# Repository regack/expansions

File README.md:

expansions
==========

Keyboard Expansion Boards

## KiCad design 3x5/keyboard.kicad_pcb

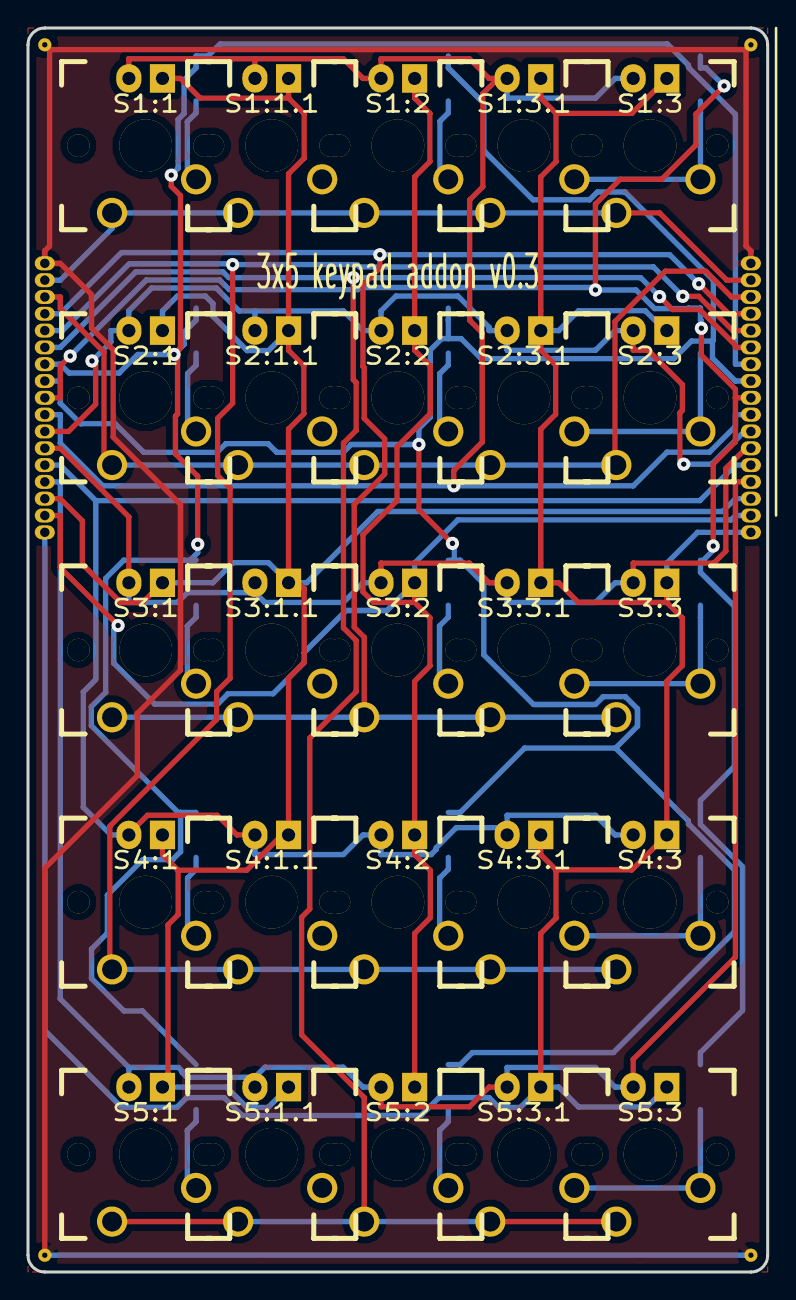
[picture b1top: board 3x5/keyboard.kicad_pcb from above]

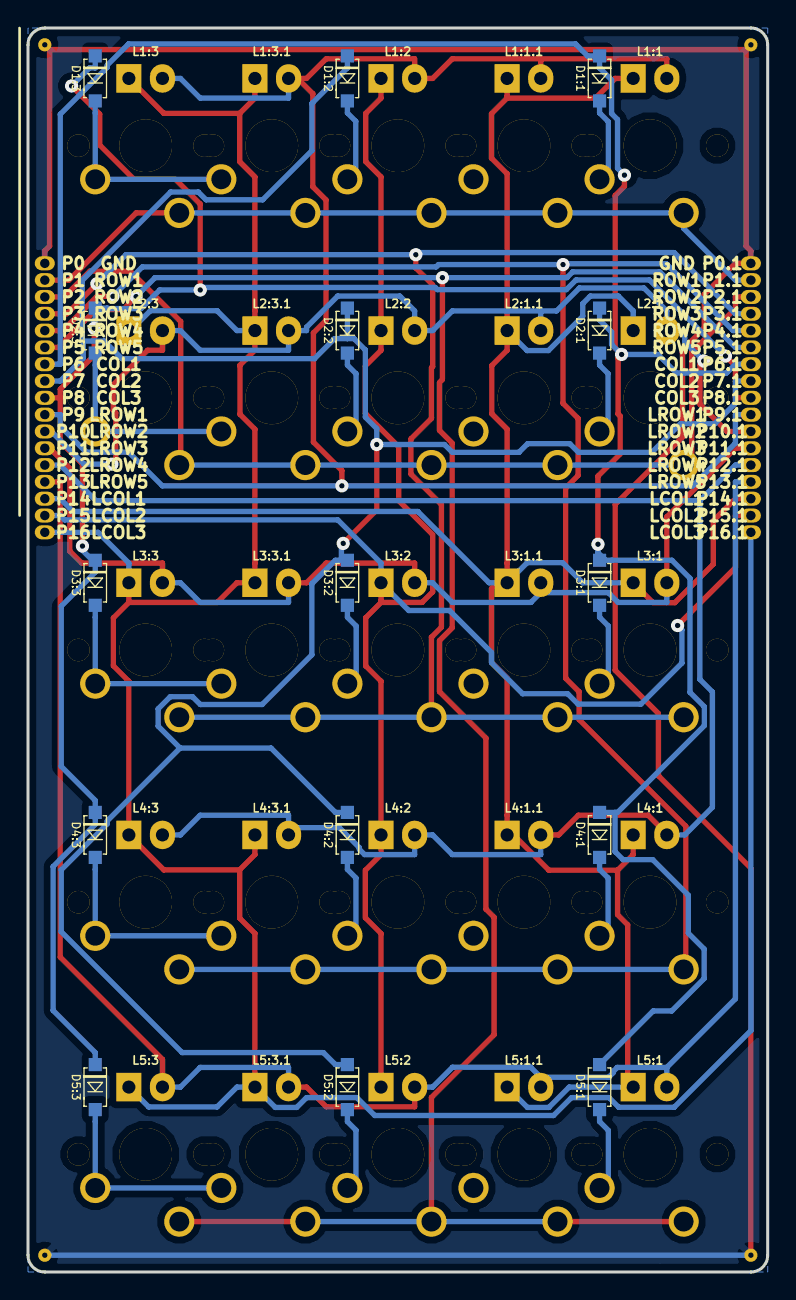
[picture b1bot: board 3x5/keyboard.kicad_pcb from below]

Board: 2 copper layers, 55.9 x 94.0 mm, 103 parts (74 on the bottom side), 32 nets.

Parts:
D1:1, D1:2, D1:3, D2:1, D2:2, D2:3, D3:1, D3:2, D3:3, D4:1, D4:2, D4:3, D5:1, D5:2, D5:3: 1N4148; SOD-123(A-C)
L1:1, L1:1.1, L1:2, L1:3, L1:3.1, L2:1, L2:1.1, L2:2, L2:3, L2:3.1, L3:1, L3:1.1, L3:2, L3:3, L3:3.1, L4:1, L4:1.1, L4:2, L4:3, L4:3.1, L5:1, L5:1.1, L5:2, L5:3, L5:3.1: LED; CHERRY_MX_LED
P0, P0.1: GND; Pad_50mil
P1, P1.1: ROW1; Pad_50mil
P2, P2.1: ROW2; Pad_50mil
P3, P3.1: ROW3; Pad_50mil
P4, P4.1: ROW4; Pad_50mil
P5, P5.1: ROW5; Pad_50mil
P6, P6.1: COL1; Pad_50mil
P7, P7.1: COL2; Pad_50mil
P8, P8.1: COL3; Pad_50mil
P9, P9.1: LROW1; Pad_50mil
P10, P10.1: LROW2; Pad_50mil
P11, P11.1: LROW3; Pad_50mil
P12, P12.1: LROW4; Pad_50mil
P13, P13.1: LROW5; Pad_50mil
P14, P14.1: LCOL1; Pad_50mil
P15, P15.1: LCOL2; Pad_50mil
P16, P16.1: LCOL3; Pad_50mil
P100, P101, P102, P103: GND; Pad_Gnd
S1:1, S1:1.1, S1:2, S1:3, S1:3.1, S2:1, S2:1.1, S2:2, S2:3, S2:3.1, S3:1, S3:1.1, S3:2, S3:3, S3:3.1, S4:1, S4:1.1, S4:2, S4:3, S4:3.1, S5:1, S5:1.1, S5:2, S5:3, S5:3.1: MX1A; CHERRY_PCB_100H_Plated

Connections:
GND: P0.1, P0.1.1, P100.1, P101.1, P102.1, P103.1
unnamed: L3:1.C, L3:1.1.C, L3:2.C, L3:3.C, L3:3.1.C, P11.1, P11.1.1
unnamed: L5:1.C, L5:1.1.C, L5:2.C, L5:3.C, L5:3.1.C, P13.1, P13.1.1
unnamed: P5.1, P5.1.1, S5:1.1, S5:1.1.1, S5:2.1, S5:3.1, S5:3.1.1
unnamed: D5:2.C, S5:2.2
unnamed: D4:2.C, S4:2.2
unnamed: L4:1.C, L4:1.1.C, L4:2.C, L4:3.C, L4:3.1.C, P12.1, P12.1.1
unnamed: D5:3.C, S5:3.2, S5:3.1.2
unnamed: D4:3.C, S4:3.2, S4:3.1.2
unnamed: D3:3.C, S3:3.2, S3:3.1.2
unnamed: D2:3.C, S2:3.2, S2:3.1.2
unnamed: D1:3.C, S1:3.2, S1:3.1.2
unnamed: D1:2.A, D2:2.A, D3:2.A, D4:2.A, D5:2.A, P7.1, P7.1.1
unnamed: D1:2.C, S1:2.2
unnamed: L1:3.A, L1:3.1.A, L2:3.A, L2:3.1.A, L3:3.A, L3:3.1.A, L4:3.A, L4:3.1.A, L5:3.A, L5:3.1.A, P16.1, P16.1.1
unnamed: D1:3.A, D2:3.A, D3:3.A, D4:3.A, D5:3.A, P8.1, P8.1.1
unnamed: D2:2.C, S2:2.2
unnamed: D2:1.C, S2:1.2
unnamed: P2.1, P2.1.1, S2:1.1, S2:1.1.1, S2:2.1, S2:3.1, S2:3.1.1
unnamed: D1:1.C, S1:1.2
unnamed: P1.1, P1.1.1, S1:1.1, S1:1.1.1, S1:2.1, S1:3.1, S1:3.1.1
unnamed: L2:1.C, L2:1.1.C, L2:2.C, L2:3.C, L2:3.1.C, P10.1, P10.1.1
unnamed: L1:1.C, L1:1.1.C, L1:2.C, L1:3.C, L1:3.1.C, P9.1, P9.1.1
unnamed: D1:1.A, D2:1.A, D3:1.A, D4:1.A, D5:1.A, P6.1, P6.1.1
unnamed: D5:1.C, S5:1.2
unnamed: D4:1.C, S4:1.2
unnamed: D3:2.C, S3:2.2
unnamed: D3:1.C, S3:1.2
unnamed: P3.1, P3.1.1, S3:1.1, S3:1.1.1, S3:2.1, S3:3.1, S3:3.1.1
unnamed: L1:2.A, L2:2.A, L3:2.A, L4:2.A, L5:2.A, P15.1, P15.1.1
unnamed: L1:1.A, L1:1.1.A, L2:1.A, L2:1.1.A, L3:1.A, L3:1.1.A, L4:1.A, L4:1.1.A, L5:1.A, L5:1.1.A, P14.1, P14.1.1
unnamed: P4.1, P4.1.1, S4:1.1, S4:1.1.1, S4:2.1, S4:3.1, S4:3.1.1

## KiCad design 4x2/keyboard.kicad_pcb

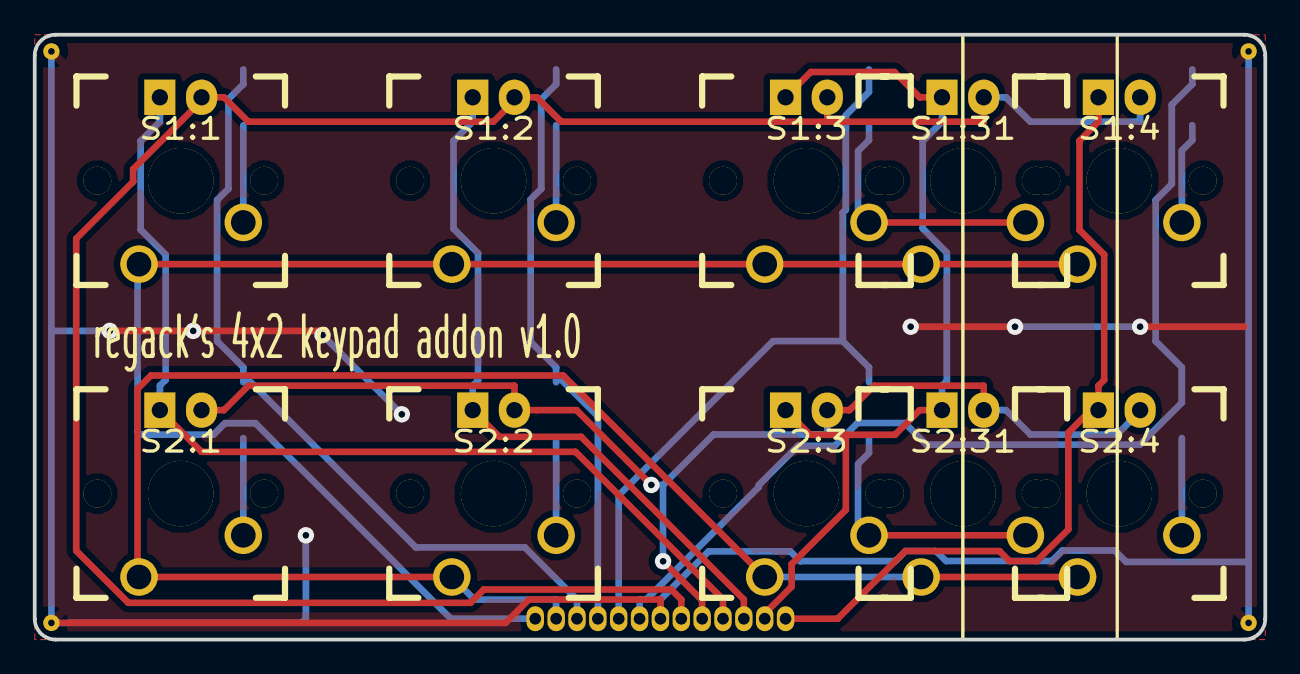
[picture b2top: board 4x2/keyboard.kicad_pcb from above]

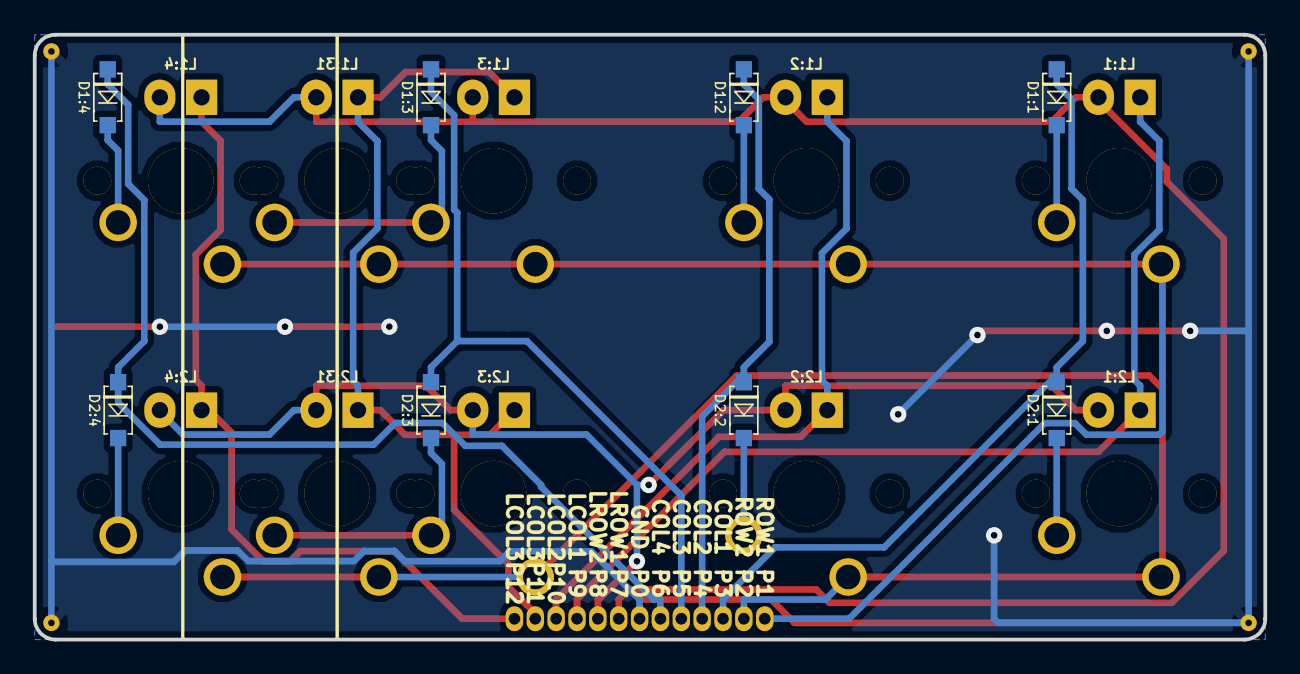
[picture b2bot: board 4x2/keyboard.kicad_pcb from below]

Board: 2 copper layers, 74.9 x 36.8 mm, 45 parts (21 on the bottom side), 21 nets.

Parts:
D1:1, D1:2, D1:3, D1:4, D2:1, D2:2, D2:3, D2:4: 1N4148; SOD-123(A-C)
L1:1, L1:2, L1:3, L1:4, L1:31, L2:1, L2:2, L2:3, L2:4, L2:31: LED; CHERRY_MX_LED
P0: GND; Pad_50mil
P1: ROW1; Pad_50mil
P2: ROW2; Pad_50mil
P3: COL1; Pad_50mil
P4: COL2; Pad_50mil
P5: COL3; Pad_50mil
P6: COL4; Pad_50mil
P7: LROW1; Pad_50mil
P8: LROW2; Pad_50mil
P9: LCOL1; Pad_50mil
P10: LCOL2; Pad_50mil
P11, P12: LCOL3; Pad_50mil
P100, P101, P102, P103: GND; Pad_Gnd
S1:1, S1:2, S1:3, S1:4, S1:31, S2:1, S2:2, S2:3, S2:4, S2:31: MX1A; CHERRY_PCB_100H_Plated

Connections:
GND: P0.1, P100.1, P101.1, P102.1, P103.1
unnamed: D1:4.C, S1:4.2
unnamed: D2:4.C, S2:4.2
unnamed: D1:3.A, D2:3.A, P5.1
unnamed: D1:3.C, S1:3.2, S1:31.2
unnamed: D1:4.A, D2:4.A, P6.1
unnamed: L1:4.A, L2:4.A, P12.1
unnamed: L1:3.A, L1:31.A, L2:3.A, L2:31.A, P11.1
unnamed: D2:2.C, S2:2.2
unnamed: D1:1.C, S1:1.2
unnamed: D1:2.C, S1:2.2
unnamed: D2:1.C, S2:1.2
unnamed: D1:1.A, D2:1.A, P3.1
unnamed: D1:2.A, D2:2.A, P4.1
unnamed: P2.1, S2:1.1, S2:2.1, S2:3.1, S2:4.1, S2:31.1
unnamed: D2:3.C, S2:3.2, S2:31.2
unnamed: P1.1, S1:1.1, S1:2.1, S1:3.1, S1:4.1, S1:31.1
unnamed: L1:1.A, L2:1.A, P9.1
unnamed: L1:1.C, L1:2.C, L1:3.C, L1:4.C, L1:31.C, P7.1
unnamed: L2:1.C, L2:2.C, L2:3.C, L2:4.C, L2:31.C, P8.1
unnamed: L1:2.A, L2:2.A, P10.1

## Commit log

2014-01-21 v0.1
2014-01-21 v0.3
